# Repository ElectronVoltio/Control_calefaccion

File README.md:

# Control_calefaccion
Documentación relacionada con el control de temperatura para la calefacción de casa

Video: https://youtu.be/ExIEtjwelSU

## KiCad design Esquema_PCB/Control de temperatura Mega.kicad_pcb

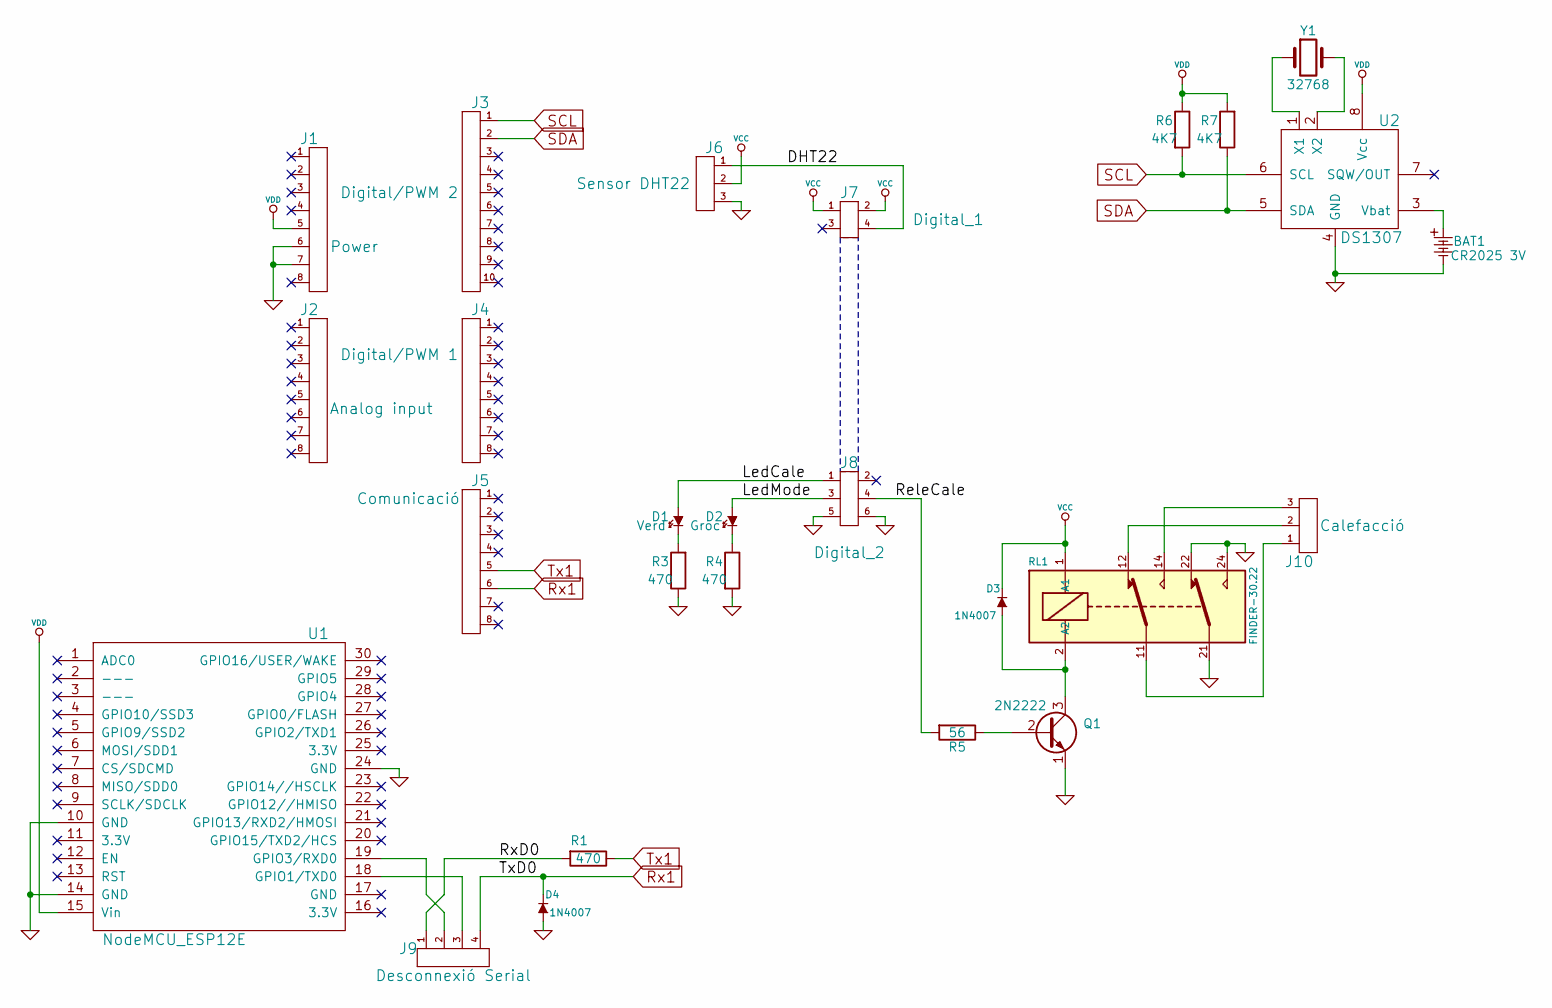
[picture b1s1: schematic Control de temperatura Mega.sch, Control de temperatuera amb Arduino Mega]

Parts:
BAT1: CR2025 3V; keystone_103
D1: Verd; Led_3mm_verd
D2: Groc; Led_3mm_groc
D3, D4: 1N4007; diode_do35
J1: Power; pin_socket_8
J2: Analog input; pin_socket_8
J3: Digital/PWM 2; pin_socket_10
J4: Digital/PWM 1; pin_socket_8
J5: Comunicació; pin_socket_8
J6: Sensor DHT22; pin_socket_3
J7: Digital_1; pin_strip_2x2
J8: Digital_2; pin_strip_3x2
J9: Desconnexió Serial; Pin_Header_Angled_1x04_Pitch2.54mm
J10: Calefacció; mkds_1,5-3
Q1: 2N2222; to18_1
R1, R3, R4: 470; RC05
R5: 56; RC05
R6, R7: 4K7; RC05
RL1: FINDER-30.22; Rele_30.22
U1: NodeMCU_ESP12E
U2: DS1307; dil_8-300_socket
Y1: 32768; Crystal_AT310_d3.0mm_l10.0mm_Horizontal

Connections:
/DHT22: J6.1, J7.4
/LedCale: D1.1 (A), J8.1
/LedMode: D2.1 (A), J8.3
/ReleCale: J8.4, R5.2
/RxD0: J9.1, R1.2
GND: BAT1.2, D4.1 (A), J1.6, J1.7, J6.3, J8.5, J8.6, Q1.1 (E), R3.1, R4.2, RL1.21, RL1.22, RL1.24, U1.10 (GND), U1.14 (GND), U1.24 (GND), U2.4 (GND)
unnamed: BAT1.1, U2.3 (Vbat)
unnamed: D1.2 (K), R3.2
unnamed: D2.2 (K), R4.1
unnamed: D3.1 (A), Q1.3 (C), RL1.2 (A2)
unnamed: J9.2, U1.19 (GPIO3/RXD0)
unnamed: J9.3, U1.18 (GPIO1/TXD0)
unnamed: J10.1, RL1.11
unnamed: J10.2, RL1.12
unnamed: J10.3, RL1.14
unnamed: Q1.2 (B), R5.1
unnamed: U2.1 (X1), Y1.1
unnamed: U2.2 (X2), Y1.2
Rx1: D4.2 (K), J5.6, J9.4
SCL: J3.1, R6.2, U2.6 (SCL)
SDA: J3.2, R7.1, U2.5 (SDA)
Tx1: J5.5, R1.1
VCC: D3.2 (K), J6.2, J7.1, J7.2, RL1.1 (A1)
VDD: J1.5, R6.1, R7.2, U1.15 (Vin), U2.8 (Vcc)

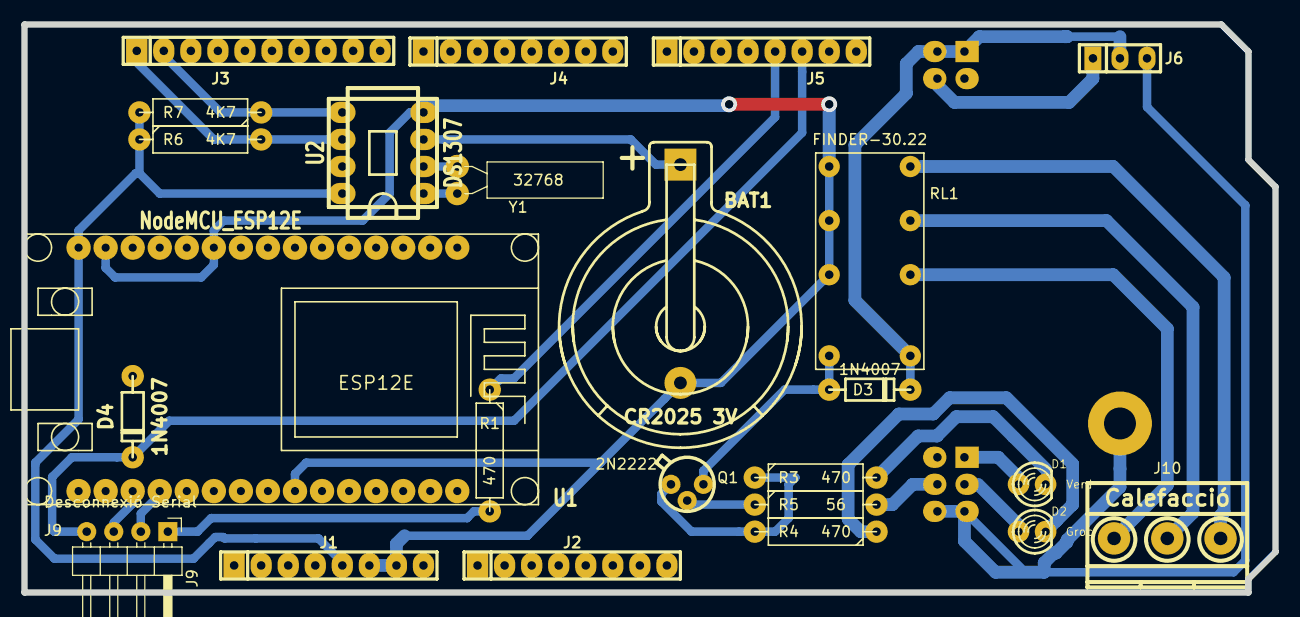
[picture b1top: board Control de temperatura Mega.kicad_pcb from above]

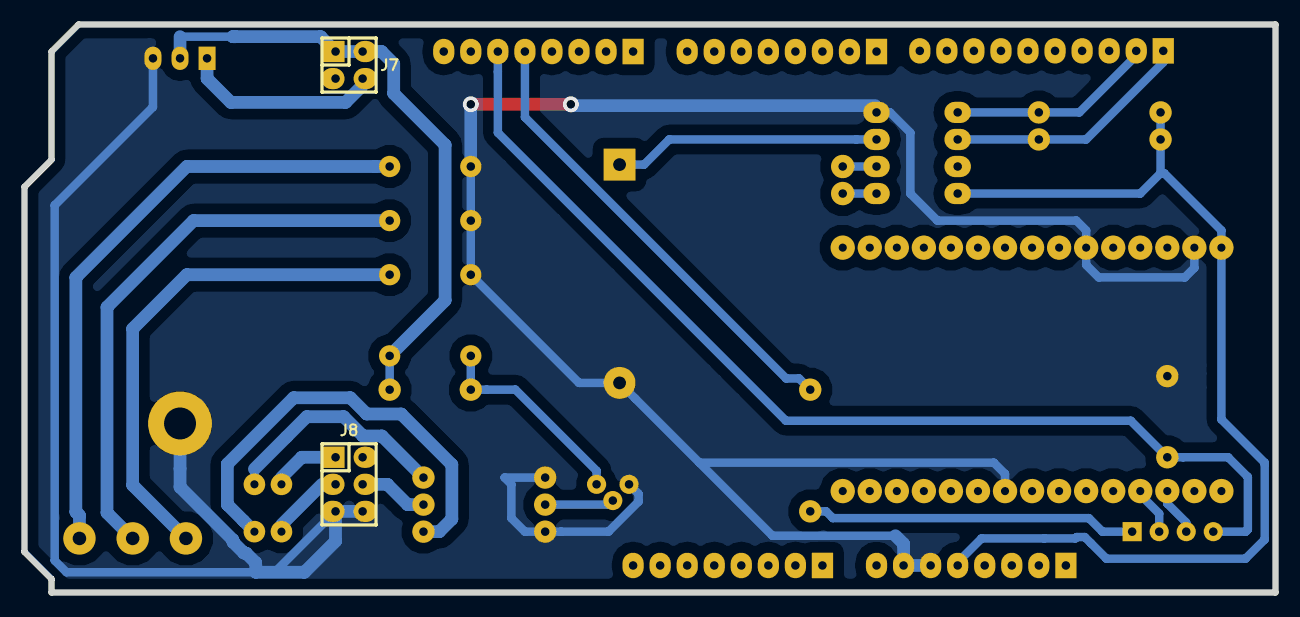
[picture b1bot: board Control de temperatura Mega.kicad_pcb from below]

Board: 2 copper layers, 117.5 x 53.3 mm, 26 parts (2 on the bottom side), 24 nets.

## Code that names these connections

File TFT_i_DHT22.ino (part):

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#include <TouchScreen.h>

//#define USE_ADAFRUIT_SHIELD_PINOUT
#define DHTTYPE DHT22

#define LCD_CS A3 // Chip Select goes to Analog 3
#define LCD_CD A2 // Command/Data goes to Analog 2
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unsigned long temporiza_C = millis(); // Variable del temps de permanència en mode manual(Per evitar que la calefacció es pogui quedar encesa
//unsigned long temporiza_D = millis();

const int ledMode = 53;   //Sortida per al LED que indica que el mode automàtic està actiu
const int releCale = 52;  //Sortida per activar el relé i en LED de la calefacció
const int ledCale = 51;   // Sortida per al LED que indica que la calefacción està en marxa

int minuts, hores, dies, mesos, anys;
int minuts_inicial, hora_inicial, dies_inicial, mesos_inicial, anys_inicial;
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    rtc.adjust(DateTime(F(__DATE__), F(__TIME__)));
  }

  pinMode(ledMode, OUTPUT);
  pinMode(releCale, OUTPUT);
  pinMode(ledCale, OUTPUT);

  Serial1.begin(115200);
  dht.begin();
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
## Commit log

2018-01-03 Create Programa_Arduino
2018-01-06 Create Rearme-md
